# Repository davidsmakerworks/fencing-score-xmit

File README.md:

# fencing-score-xmit
Remote fencing scoring light display transmitter

This project is used to transmit the display from a fencing scoring machine to up to four remote displays, which could be wall lights or in-mask lights. A fencing scoring machine display consists of four lights from left to right: white, red, green, white. The red light indicates a valid hit by the fencer on the left and the green light indicates a valid hit by the fencer on the right. The corresponding white (or yellow) lights indicate a an off-target hit or equipment malfunction for the fencer on that side.

This was designed to work with a Triplette Club Scoring machine which I reverse engineered to discover the gate on each MOSFET that drives one of the lights. Inputs to the the transmitter module are soldered to the corresponding gate on the MOSFET allowing the signal to be observed without affecting the function of the scoring machine.

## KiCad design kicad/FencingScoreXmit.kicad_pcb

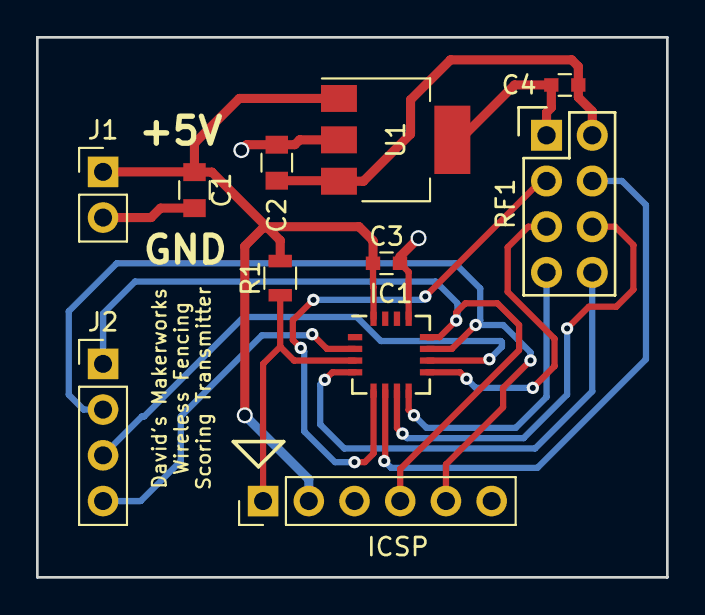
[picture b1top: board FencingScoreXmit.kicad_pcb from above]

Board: 2 copper layers, 35.0 x 30.0 mm, 11 parts (0 on the bottom side), 14 nets.

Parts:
C1: 10uF; C_0805
C2: 1uF; C_0805
C3, C4: 0.1uF; C_0603
IC1: PIC16F18323-I/JQ; QFN-16-1EP_4x4mm_Pitch0.65mm
ICSP: ICSP; Pin_Header_Straight_1x06_Pitch2.54mm
J1: PWR_IN; Pin_Header_Straight_1x02_Pitch2.54mm
J2: SCORE_MACH; Pin_Header_Straight_1x04_Pitch2.54mm
R1: 10K; R_0805
RF1: nRF24L01+-MOD; nRF24L01+-Module
U1: MCP1824S33/DB; SOT-223

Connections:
+3V3: C2.1, C4.1, RF1.2, U1.3
+5V: C1.1, C3.1, IC1.16, ICSP.2, J1.1, R1.2, U1.1
GND: C1.2, C2.2, C3.2, C4.2, IC1.13, ICSP.3, J1.2, RF1.1, U1.2, U1.4
unnamed: IC1.2, J2.4
unnamed: IC1.3, ICSP.1, R1.1
unnamed: IC1.4, RF1.8
unnamed: IC1.5, RF1.3
unnamed: IC1.6, RF1.4
unnamed: IC1.7, RF1.6
unnamed: IC1.8, RF1.7
unnamed: IC1.9, RF1.5
unnamed: IC1.10, J2.3
unnamed: IC1.11, ICSP.5, J2.2
unnamed: IC1.12, ICSP.4, J2.1

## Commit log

2019-06-24 Add MIT license
2019-06-25 Add legacy AVR ASM file from previous version of project
2019-06-26 Update for compatibility with restructured driver
2019-12-17 Update DFP
2020-11-20 Update DFP and compiler version
2020-12-25 Remove unnecessary files
2023-03-18 Update RF addr and silkscreen, update for KiCad 7
